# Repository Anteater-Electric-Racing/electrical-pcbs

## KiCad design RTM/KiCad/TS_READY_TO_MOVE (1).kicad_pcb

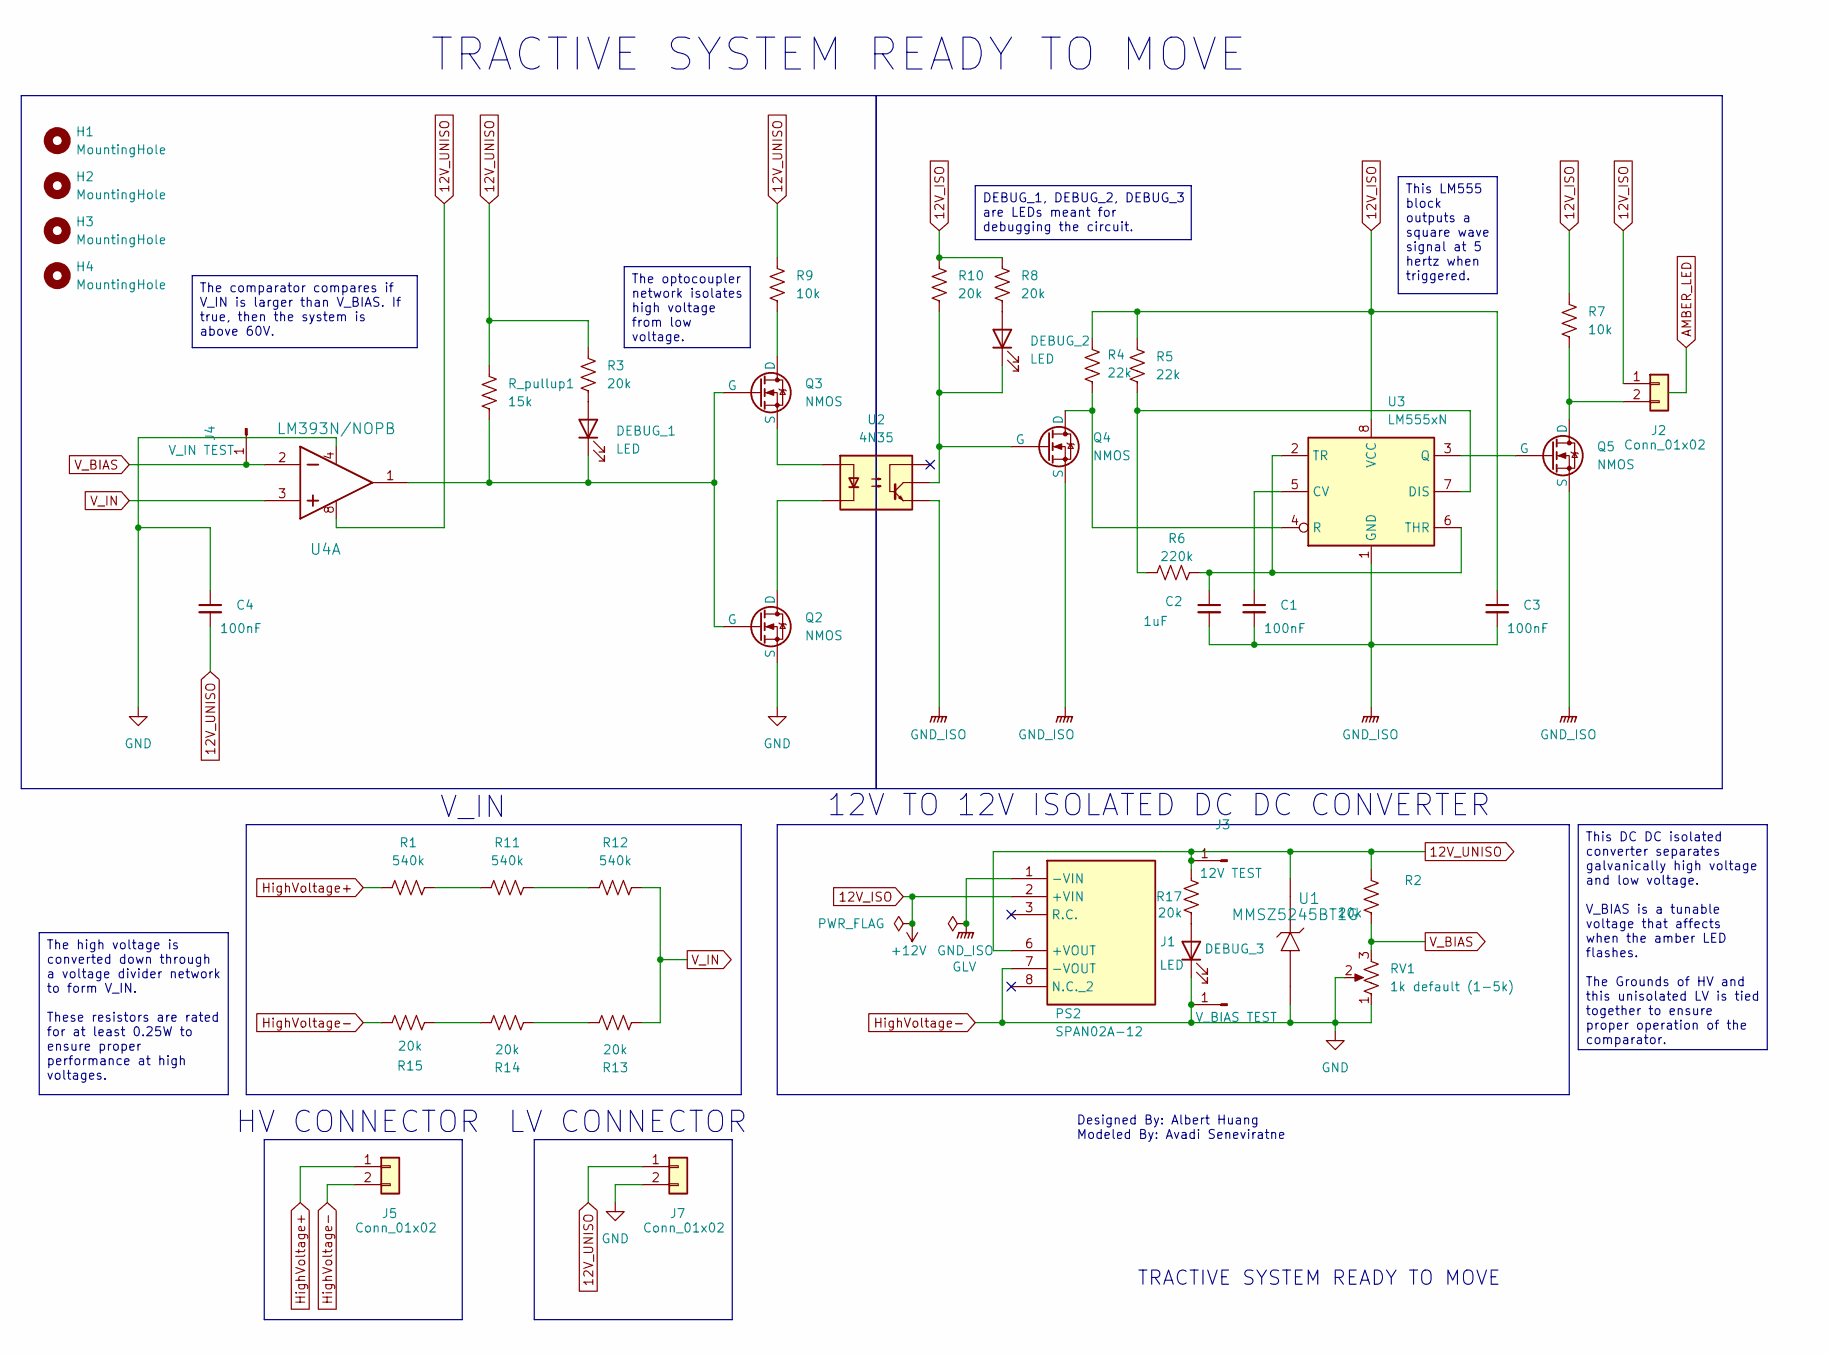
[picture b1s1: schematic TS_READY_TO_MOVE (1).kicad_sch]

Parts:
C1, C3, C4: 100nF; C_0805_2012Metric
C2: 1uF; C_0805_2012Metric
DEBUG_1, DEBUG_2, DEBUG_3: LED; LED_D5.0mm
H1, H2, H3, H4: MountingHole; MountingHole_3.2mm_M3
J1: V_BIAS TEST; TestPoint_Loop_D3.80mm_Drill2.0mm
J2, J5, J7: Conn_01x02; Molex_Mini-Fit_Jr_5566-02A2_2x01_P4.20mm_Vertical
J3: 12V TEST; TestPoint_Loop_D3.80mm_Drill2.0mm
J4: V_IN TEST; TestPoint_Loop_D3.80mm_Drill2.0mm
PS2: SPAN02A-12; SPAN02A12; Mouser Part Number 709-SPAN02A-12
Q2, Q3, Q4, Q5: NMOS; TO-220-3_Vertical
R1, R11, R12: 540k; R_0805_2012Metric
R2, R3, R8, R10, R13, R14, R15, R17: 20k; R_0805_2012Metric
R4, R5: 22k; R_0805_2012Metric
R6: 220k; R_0805_2012Metric
R7, R9: 10k; R_0805_2012Metric
RV1: 1k default (1-5k); Potentiometer_Bourns_3296Y_Vertical
R_pullup1: 15k; R_0805_2012Metric
U1: MMSZ5245BT1G; D_SOD-123
U2: 4N35; DIP-6_W7.62mm
U3: LM555xN; DIP-8_W7.62mm
U4: LM393N/NOPB; DIP-8_W7.62mm

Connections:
12V_ISO: C3.1, J2.1, PS2.2 (+VIN), R4.1, R5.1, R7.1, R8.1, R10.1, U3.8 (VCC)
GND_ISO: C1.2, C2.2, C3.2, PS2.1 (-VIN), Q4.3 (S), Q5.3 (S), U2.4, U3.1 (GND)
HighVoltage+: J5.1, R1.1
HighVoltage-: C4.1, DEBUG_3.1 (K), J1.1, J5.2, J7.2, PS2.7 (-VOUT), Q2.3 (S), R15.2, RV1.1, RV1.2, U1.2 (ANODE), U4.4 (GND); also elsewhere on the board
unnamed: DEBUG_1.2 (A), R3.2
unnamed: DEBUG_1.1 (K), Q2.2 (G), Q3.2 (G), R_pullup1.2, U4.1 (OUT)
unnamed: DEBUG_2.2 (A), R8.2
unnamed: DEBUG_2.1 (K), Q4.2 (G), R10.2, U2.5
unnamed: DEBUG_3.2 (A), R17.2
unnamed: J2.2, Q5.1 (D), R7.2
unnamed: Q2.1 (D), U2.2
unnamed: Q3.1 (D), R9.2
unnamed: Q3.3 (S), U2.1
unnamed: Q4.1 (D), R4.2, U3.4 (R)
unnamed: Q5.2 (G), U3.3 (Q)
unnamed: R1.2, R11.2
unnamed: R11.1, R12.1
unnamed: R13.2, R14.2
unnamed: R14.1, R15.1
unnamed: C1.1, U3.5 (CV)
unnamed: R5.2, R6.1, U3.7 (DIS)
unnamed: C2.1, R6.2, U3.2 (TR), U3.6 (THR)
V_IN: R12.2, R13.1, U4.3 (IN+)

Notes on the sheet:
12V TO 12V ISOLATED DC DC CONVERTER
V_IN
TRACTIVE SYSTEM READY TO MOVE
LV CONNECTOR
TRACTIVE SYSTEM READY TO MOVE
Designed By: Albert Huang Modeled By: Avadi Seneviratne
HV CONNECTOR
This DC DC isolated converter separates galvanically high voltage and low voltage. V_BIAS is a tunable voltage that affects when the amber LED flashes. The Grounds of HV and this unisolated LV is tied together to ensure proper operation of the comparator.
The comparator compares if V_IN is larger than V_BIAS. If true, then the system is above 60V.
The high voltage is converted down through a voltage divider network to form V_IN. These resistors are rated for at least 0.25W to ensure proper performance at high voltages.
This LM555 block outputs a square wave signal at 5 hertz when triggered.
DEBUG_1, DEBUG_2, DEBUG_3 are LEDs meant for debugging the circuit.
The optocoupler network isolates high voltage from low voltage.

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
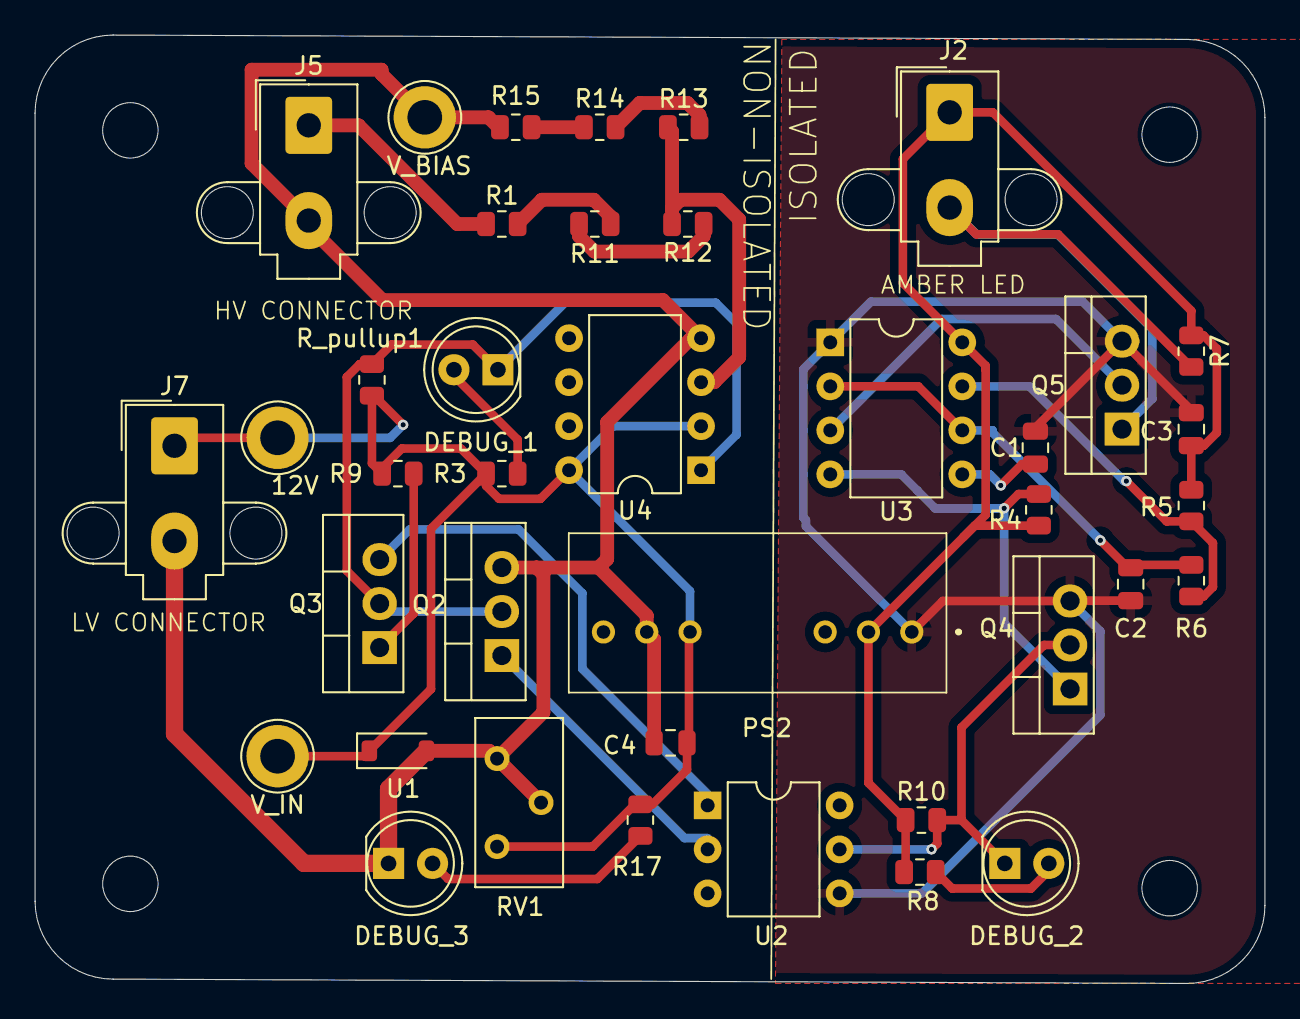
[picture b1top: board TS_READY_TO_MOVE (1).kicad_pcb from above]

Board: 2 copper layers, 71.0 x 54.8 mm, 43 parts (0 on the bottom side), 24 nets.

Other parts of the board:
12V: 12V TEST; TestPoint_Loop_D3.80mm_Drill2.0mm
V_BIAS: V_BIAS TEST; TestPoint_Loop_D3.80mm_Drill2.0mm
V_IN: V_IN TEST; TestPoint_Loop_D3.80mm_Drill2.0mm

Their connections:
HighVoltage-: V_BIAS.1; also elsewhere on the board

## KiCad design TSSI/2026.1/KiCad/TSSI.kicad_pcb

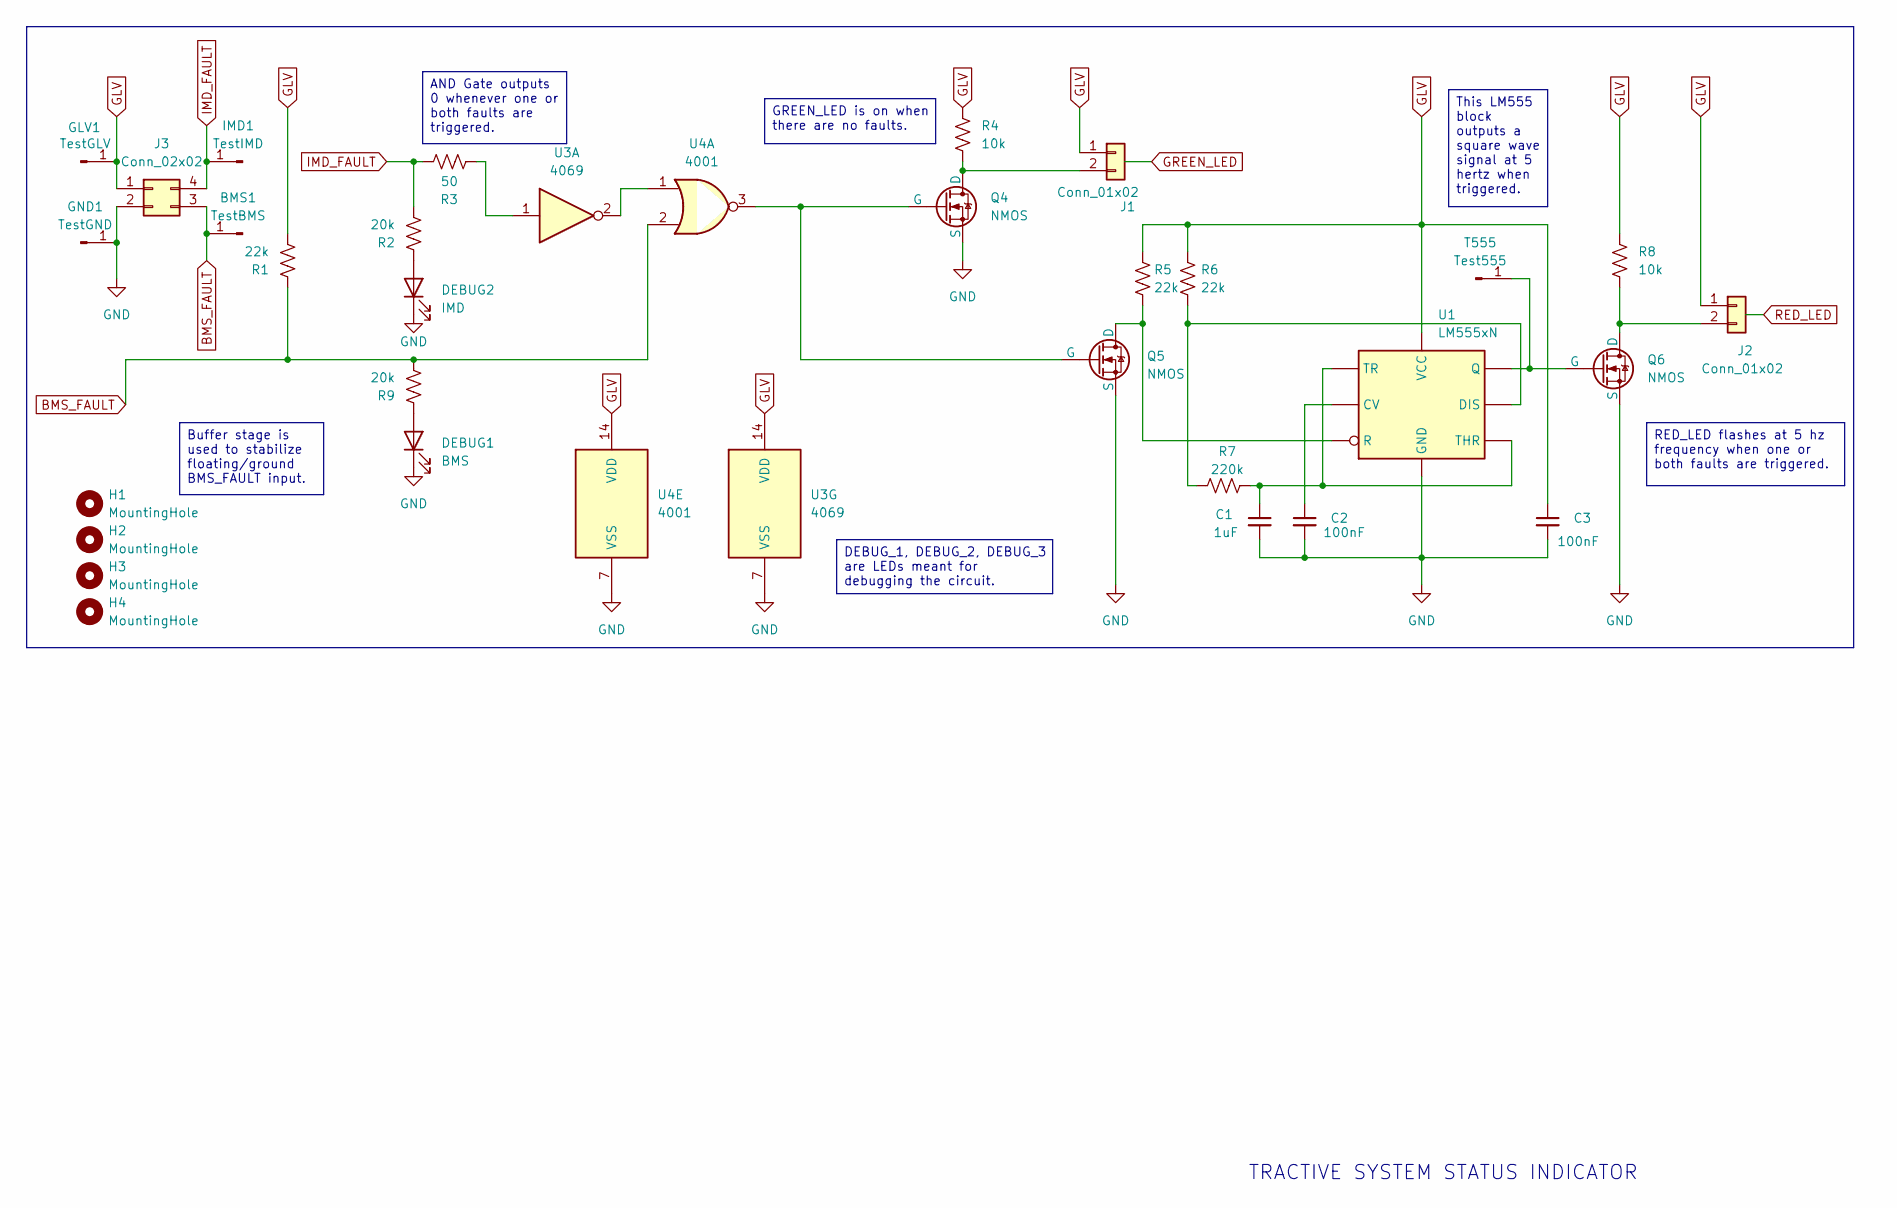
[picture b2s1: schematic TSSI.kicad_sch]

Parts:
BMS1: TestBMS; PinHeader_1x01_P1.00mm_Vertical
C1: 1uF; C_0805_2012Metric
C2, C3: 100nF; C_0805_2012Metric
DEBUG1: BMS; LED_D4.0mm
DEBUG2: IMD; LED_D4.0mm
GLV1: TestGLV; PinHeader_1x01_P1.00mm_Vertical
GND1: TestGND; PinHeader_1x01_P1.00mm_Vertical
H1, H2, H3, H4: MountingHole; MountingHole_3.2mm_M3
IMD1: TestIMD; PinHeader_1x01_P1.00mm_Vertical
J1, J2: Conn_01x02; Molex_Mini-Fit_Jr_5566-02A_2x01_P4.20mm_Vertical
J3: Conn_02x02; Molex_Mini-Fit_Jr_5566-04A_2x02_P4.20mm_Vertical
Q4, Q5, Q6: NMOS; TO254P465X1024X2050-3P
R1, R5, R6: 22k; R_0805_2012Metric
R2, R9: 20k; R_0805_2012Metric
R3: 50; R_0805_2012Metric
R4, R8: 10k; R_0805_2012Metric
R7: 220k; R_0805_2012Metric
T555: Test555; PinHeader_1x01_P1.00mm_Vertical
U1: LM555xN; DIP-8_W7.62mm
U3: 4069; SOIC-14_3.9x8.7mm_P1.27mm
U4: 4001; SOIC-14_3.9x8.7mm_P1.27mm

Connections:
BMS_FAULT: BMS1.1, J3.3, R1.1, R9.2, U4.2
GLV: C3.1, GLV1.1, J1.1, J2.1, J3.1, R1.2, R4.1, R5.1, R6.1, R8.1, U1.8 (VCC), U3.14 (VDD), U4.14 (VDD)
GND: C1.2, C2.2, C3.2, DEBUG1.1 (K), DEBUG2.1 (K), GND1.1, J3.2, Q4.3 (S), Q5.3 (S), Q6.3 (S), U1.1 (GND), U3.7 (VSS), U4.7 (VSS)
IMD_FAULT: IMD1.1, J3.4, R2.2, R3.1
unnamed: DEBUG1.2 (A), R9.1
unnamed: DEBUG2.2 (A), R2.1
unnamed: J1.2, Q4.1 (D), R4.2
unnamed: J2.2, Q6.1 (D), R8.2
unnamed: Q4.2 (G), Q5.2 (G), U4.3
unnamed: Q5.1 (D), R5.2, U1.4 (R)
unnamed: Q6.2 (G), T555.1, U1.3 (Q)
unnamed: R3.2, U3.1
unnamed: C2.1, U1.5 (CV)
unnamed: R6.2, R7.1, U1.7 (DIS)
unnamed: C1.1, R7.2, U1.2 (TR), U1.6 (THR)
unnamed: U3.2, U4.1

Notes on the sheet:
TRACTIVE SYSTEM STATUS INDICATOR
RED_LED flashes at 5 hz frequency when one or both faults are triggered.
AND Gate outputs 0 whenever one or both faults are triggered.
This LM555 block outputs a square wave signal at 5 hertz when triggered.
GREEN_LED is on when there are no faults.
Buffer stage is used to stabilize floating/ground BMS_FAULT input.
DEBUG_1, DEBUG_2, DEBUG_3 are LEDs meant for debugging the circuit.

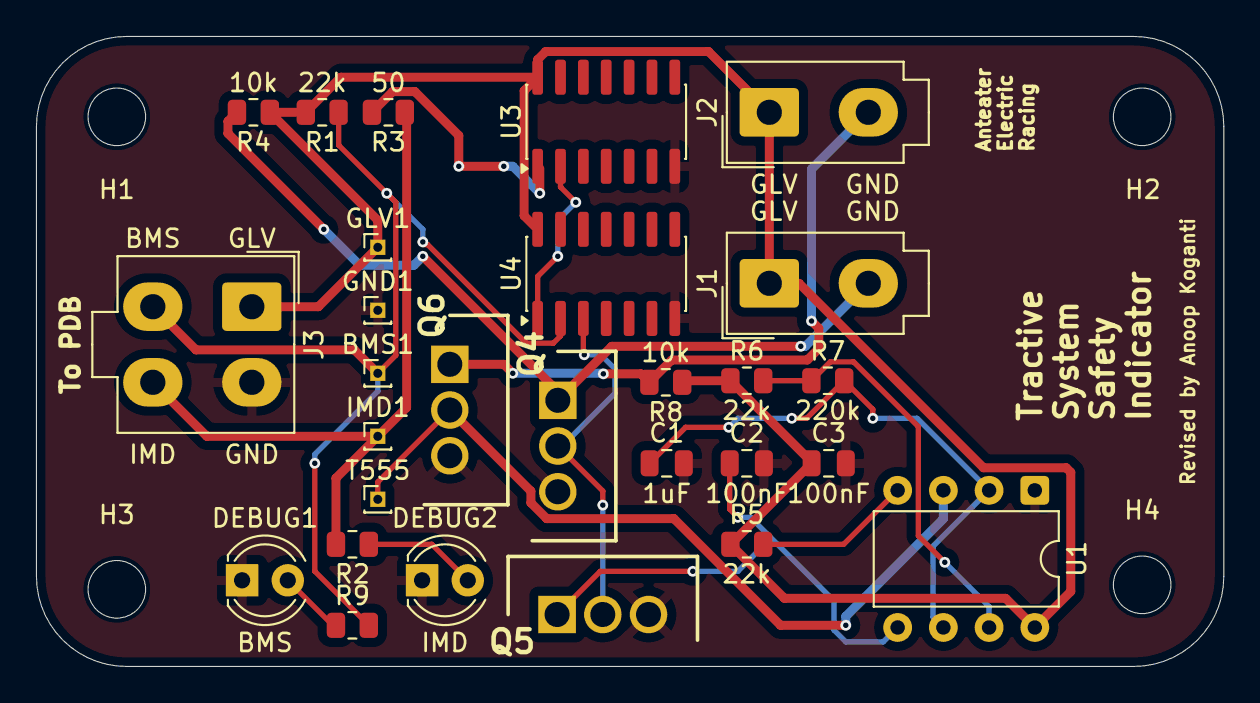
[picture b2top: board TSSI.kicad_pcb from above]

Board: 2 copper layers, 66.0 x 35.0 mm, 32 parts (0 on the bottom side), 16 nets.

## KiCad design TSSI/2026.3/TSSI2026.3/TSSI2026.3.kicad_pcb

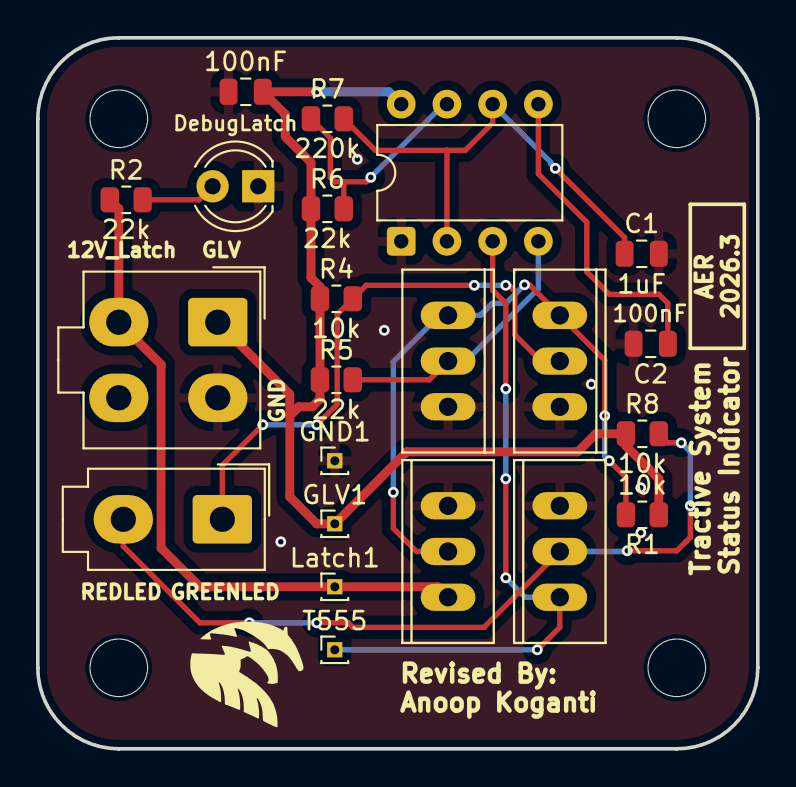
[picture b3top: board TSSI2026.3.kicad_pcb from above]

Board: 2 copper layers, 40.0 x 39.5 mm, 26 parts (0 on the bottom side), 12 nets.

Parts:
C1: 1uF; C_0805_2012Metric
C2, C3: 100nF; C_0805_2012Metric
DebugLatch: DEBUGLatch; LED_D4.0mm
GLV1: TestGLV; PinHeader_1x01_P1.00mm_Vertical
GND1: TestGND; PinHeader_1x01_P1.00mm_Vertical
H1, H2, H3, H4: MountingHole; MountingHole_3.2mm_M3
J1: Conn_02x02; Molex_Mini-Fit_Jr_5566-04A2_2x02_P4.20mm_Vertical
J2: Conn_01x02; Molex_Mini-Fit_Jr_5566-02A_2x01_P4.20mm_Vertical
Latch1: TestBMS; PinHeader_1x01_P1.00mm_Vertical
Q1, Q2, Q3: IRLZ34N; TO-220_2_
R1, R4, R8: 10k; R_0805_2012Metric
R2, R5, R6: 22k; R_0805_2012Metric
R7: 220k; R_0805_2012Metric
T555: Test555; PinHeader_1x01_P1.00mm_Vertical
U1: LM555xN; DIP-8_W7.62mm
U3: IRLZ34N; TO-220_2_

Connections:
GLV: C3.1, GLV1.1, J1.1, R1.1, R4.1, R5.1, R6.1, R8.1, U1.8 (VCC)
GND: C1.2, C2.2, C3.2, DebugLatch.1 (K), GND1.1, J1.2, Q1.OUT, Q2.OUT, Q3.OUT, U1.1 (GND), U3.OUT
GREEN_LED: J2.1, Q1.GND, R4.2
Latch_12V_Safe: J1.3, Latch1.1, Q3.IN, R2.1
unnamed: DebugLatch.2 (A), R2.2
unnamed: Q1.IN, Q2.IN, Q3.GND, R1.2
unnamed: T555.1, U1.3 (Q), U3.IN
unnamed: C2.1, U1.5 (CV)
unnamed: R6.2, R7.1, U1.7 (DIS)
unnamed: Q2.GND, R5.2, U1.4 (R)
unnamed: C1.1, R7.2, U1.2 (TR), U1.6 (THR)
RED_LED: J2.2, R8.2, U3.GND

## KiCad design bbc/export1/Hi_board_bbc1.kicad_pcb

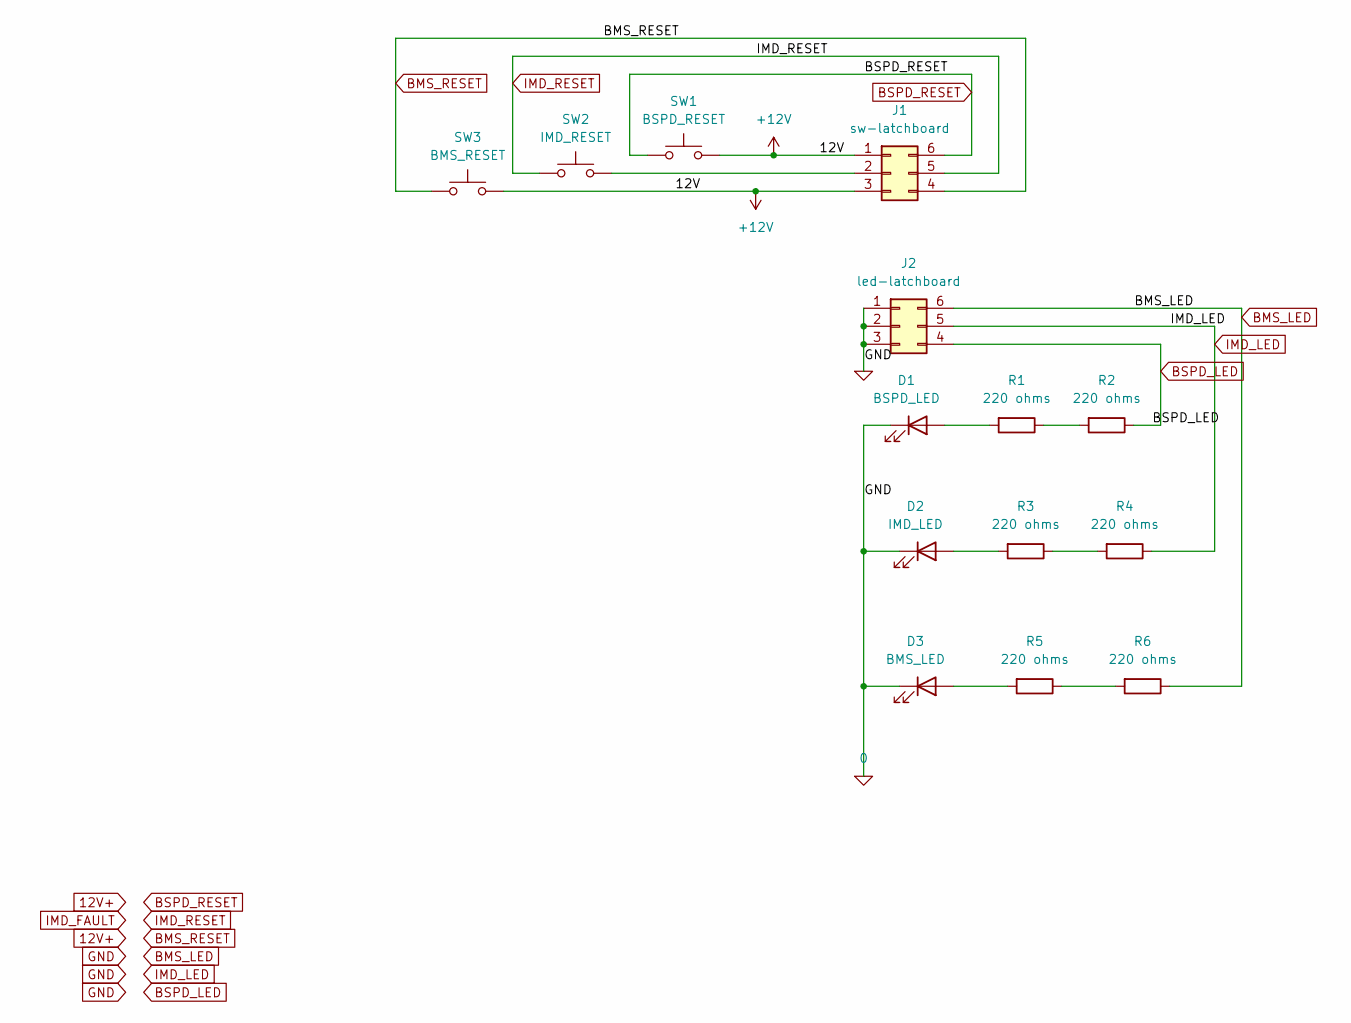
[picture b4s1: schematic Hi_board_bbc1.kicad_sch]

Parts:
D1: BSPD_LED; LED_D5.0mm
D2: IMD_LED; LED_D5.0mm
D3: BMS_LED; LED_D5.0mm
J1: sw-latchboard; Molex_Mini-Fit_Jr_5566-06A_2x03_P4.20mm_Vertical
J2: led-latchboard; Molex_Mini-Fit_Jr_5566-06A_2x03_P4.20mm_Vertical
R1, R2, R3, R4, R5, R6: 220 ohms; R_Axial_DIN0207_L6.3mm_D2.5mm_P10.16mm_Horizontal
SW1: BSPD_RESET; SW_PUSH_6mm
SW2: IMD_RESET; SW_PUSH_6mm
SW3: BMS_RESET; SW_PUSH_6mm

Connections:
+12V: J1.1, J1.3, SW1.2, SW3.2
BMS_LED: J2.6, R6.1
BMS_RESET: J1.4, SW3.1
BSPD_LED: J2.4, R2.1
BSPD_RESET: J1.6, SW1.1
GND: D1.1 (K), D2.1 (K), D3.1 (K), J2.1, J2.2, J2.3
IMD_LED: J2.5, R4.1
IMD_RESET: J1.5, SW2.1
unnamed: D1.2 (A), R1.2
unnamed: D2.2 (A), R3.2
unnamed: D3.2 (A), R5.2
unnamed: J1.2, SW2.2
unnamed: R1.1, R2.2
unnamed: R3.1, R4.2
unnamed: R5.1, R6.2

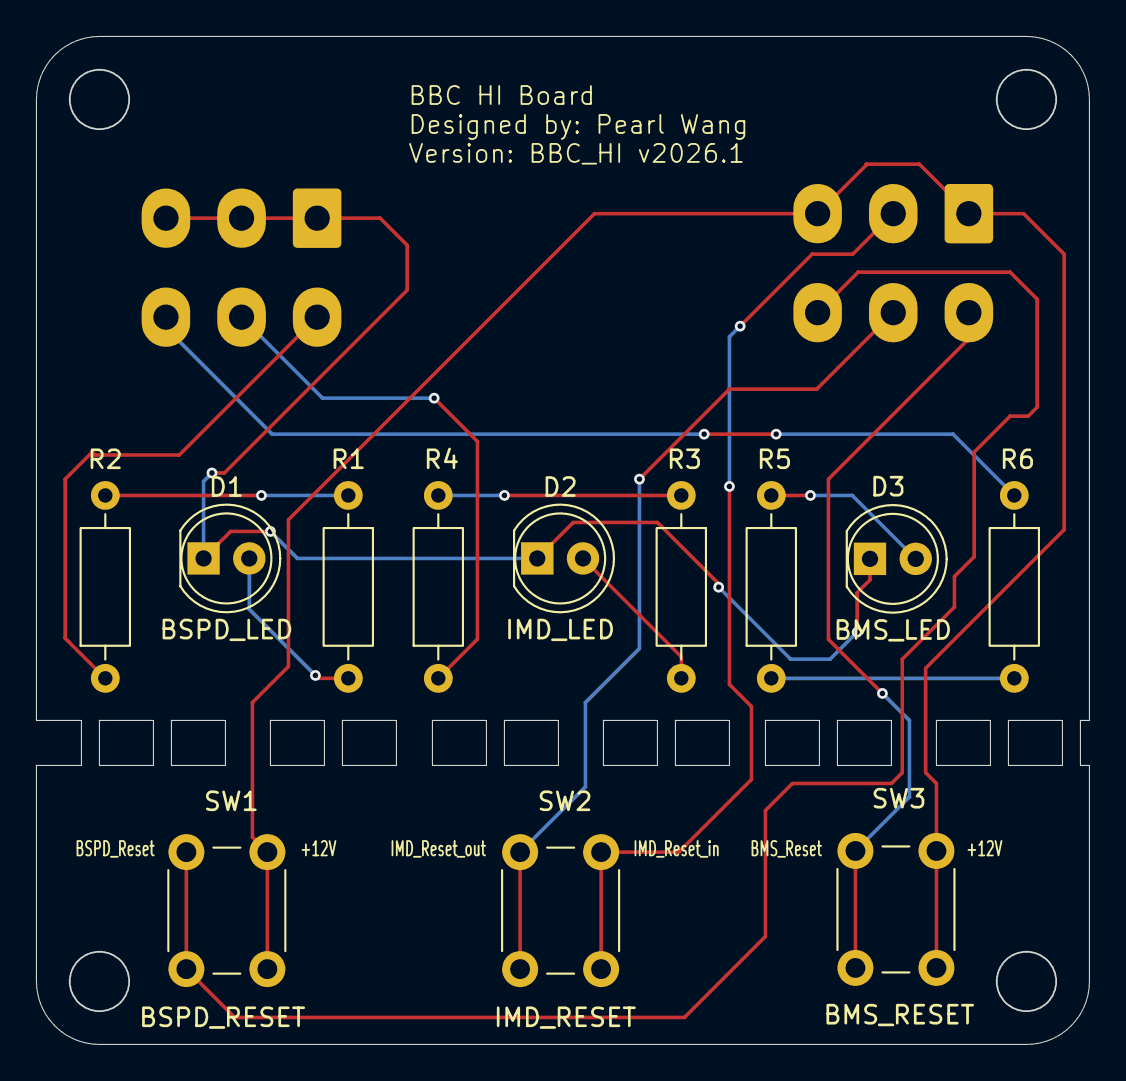
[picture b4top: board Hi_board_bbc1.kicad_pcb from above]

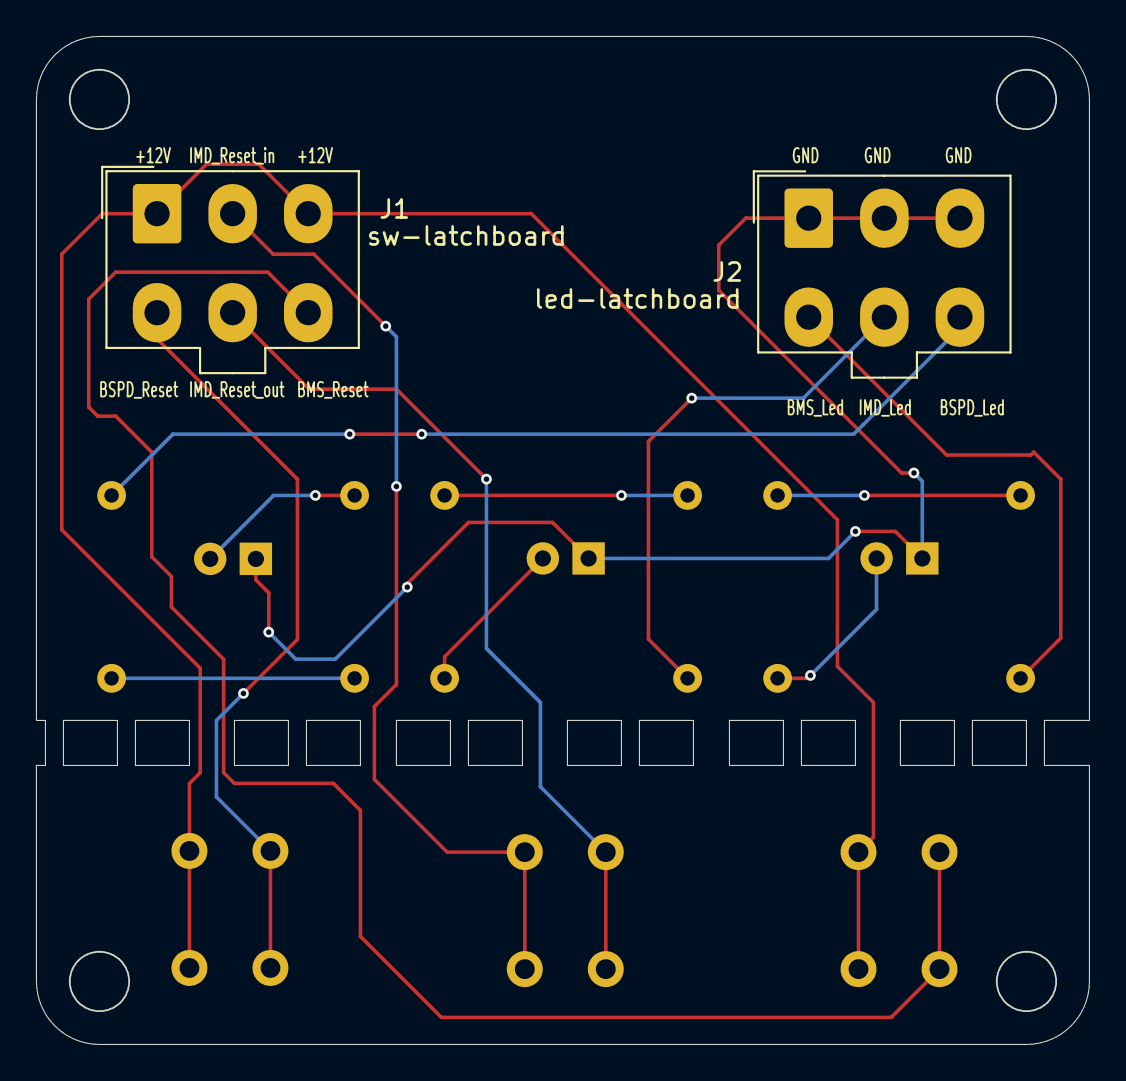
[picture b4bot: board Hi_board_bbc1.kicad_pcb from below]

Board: 2 copper layers, 58.5 x 56.0 mm, 14 parts (2 on the bottom side), 15 nets.
